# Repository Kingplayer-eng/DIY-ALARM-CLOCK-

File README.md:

# DIY-ALARM-CLOCK-
A Hardware project!!
So basically its a esp32 powered alarm clock that will show time and ring alarm in morning or anytime . There is 3.5 inch tft screen with can be use by either touch or by joystick. It has a motion detector at top - Adafruit sensor it sense hand and shut of alarm . There is also a kill switch at back which can turn off everything . It will be powered by lipo rechargeable batteries and charging module to charge it of course. I will not add buzzer as it literally irritate your hearing instead i added a amplifier with speaker . 
- I made this project specifically to lock in . I cannot wake up early with phone and then start scrolling which is really bad so i better try this .

- 
-
-
-

-PCB

-Schematic diagram

-Extra Information

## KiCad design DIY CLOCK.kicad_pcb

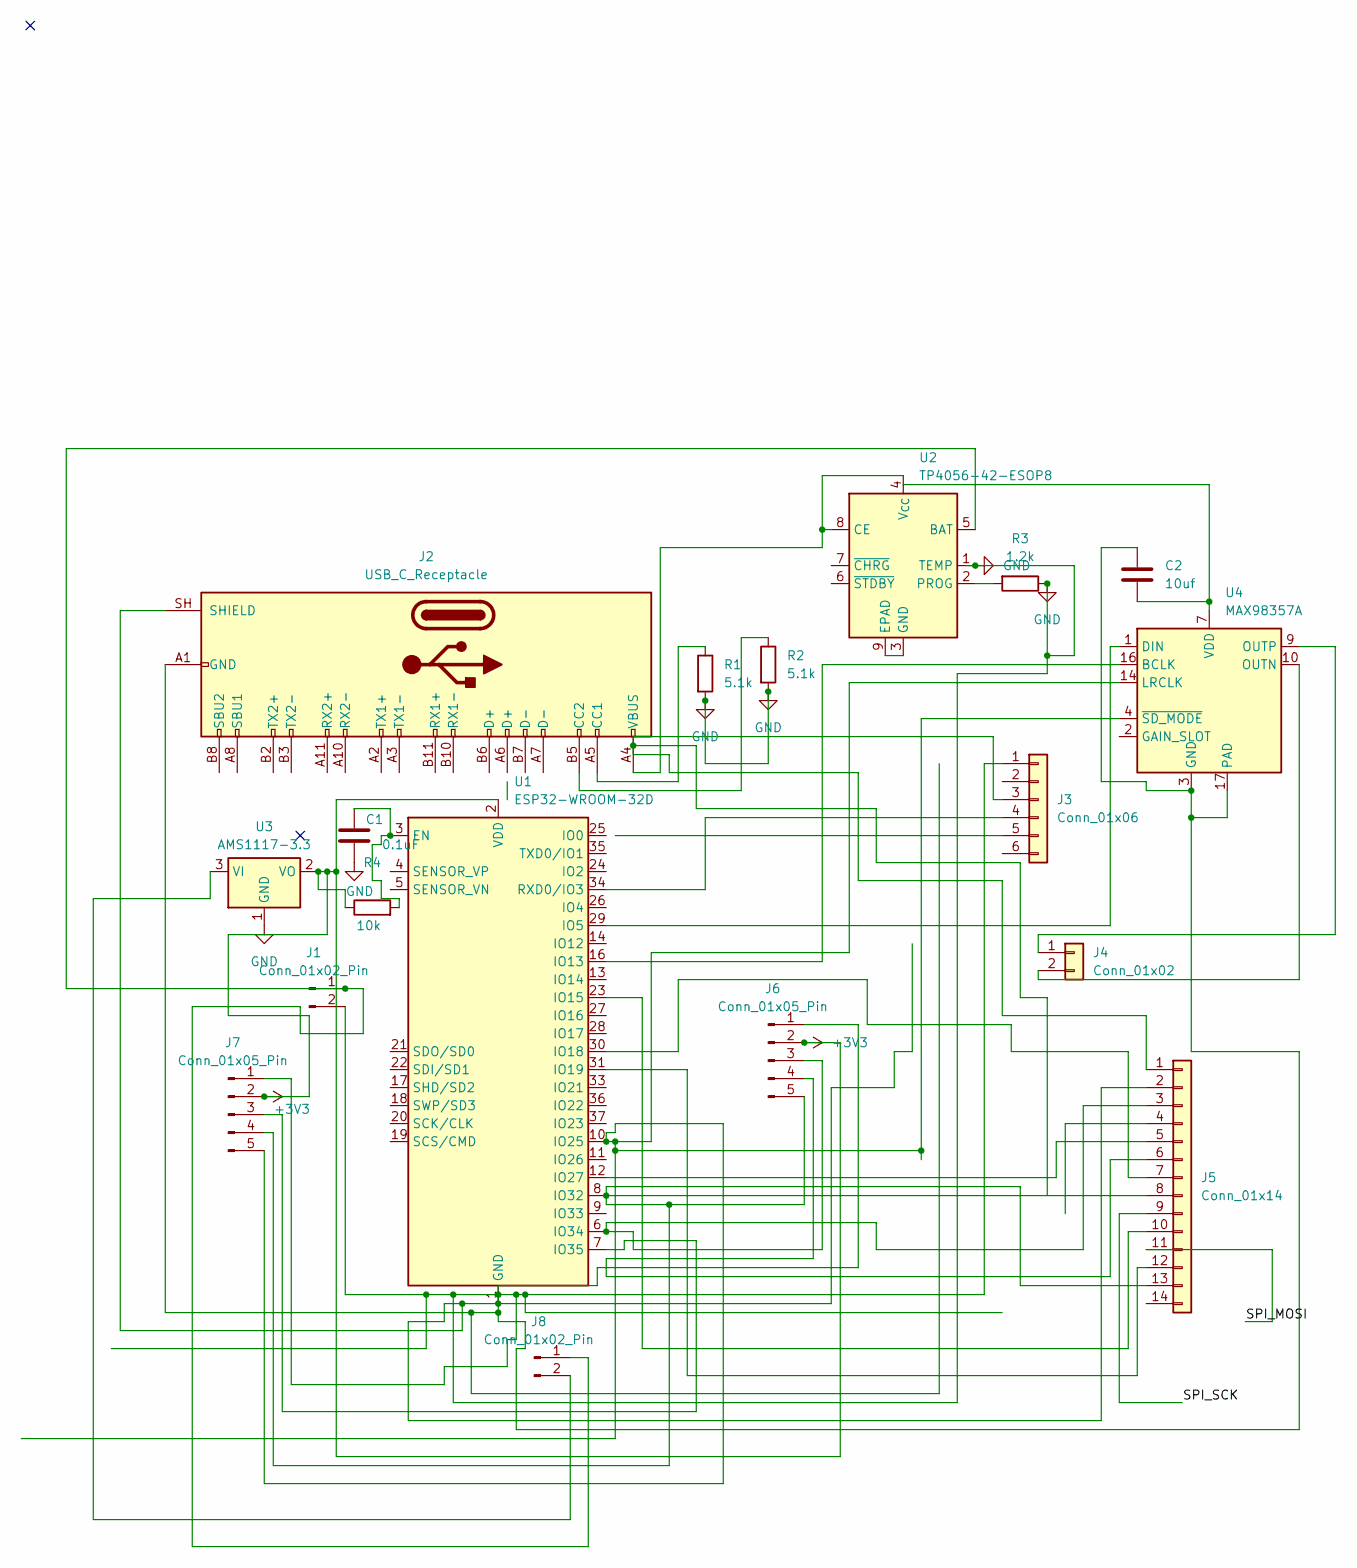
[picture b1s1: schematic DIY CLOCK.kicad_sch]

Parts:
C1: 0.1uF; C_0805_2012Metric
C2: 10uf; C_0805_2012Metric
J1: Conn_01x02_Pin; PinHeader_1x02_P2.54mm_Vertical_SMD_Pin1Left
J2: USB_C_Receptacle; USB_C_Receptacle_HRO_TYPE-C-31-M-12
J3: Conn_01x06
J4: Conn_01x02
J5: Conn_01x14; PinHeader_1x14_P2.54mm_Vertical
J6, J7: Conn_01x05_Pin; PinHeader_1x05_P2.54mm_Vertical
J8: Conn_01x02_Pin; PinHeader_1x02_P2.54mm_Vertical
R1, R2: 5.1k; R_0805_2012Metric_Pad1.20x1.40mm_HandSolder
R3: 1.2k; R_0805_2012Metric_Pad1.20x1.40mm_HandSolder
R4: 10k; R_0805_2012Metric
U1: ESP32-WROOM-32D
U2: TP4056-42-ESOP8; SOIC-8-1EP_3.9x4.9mm_P1.27mm_EP2.41x3.3mm_ThermalVias
U3: AMS1117-3.3; SOT-223-3_TabPin2
U4: MAX98357A; TQFN-16-1EP_3x3mm_P0.5mm_EP1.23x1.23mm

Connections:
+3V3: J6.2, J7.2, R4.1, U1.2 (VDD), U3.2 (VO)
/SPI_MOSI: J5.11
/SPI_SCK: J5.9
GND: C1.2, C2.1, J1.2, J2.A1 (GND), J2.A12 (GND), J2.B1 (GND), J2.B12 (GND), J2.SH (SHIELD), J3.1, J5.2, J6.1, J7.1, R1.2, R2.2, R3.1, U1.1 (GND), U1.15 (GND), U1.38 (GND), U1.39 (GND), U2.1 (TEMP), U3.1 (GND), U4.3 (GND), U4.11 (GND), U4.15 (GND), U4.17 (PAD)
unnamed: C2.2, U4.7 (VDD), U4.8 (VDD)
unnamed: J1.1, J8.1, U2.5 (BAT)
unnamed: J2.A5 (CC1), R1.1
unnamed: J2.B5 (CC2), R2.1
unnamed: J3.3, J5.1
unnamed: J3.4, U1.34 (RXD0/IO3)
unnamed: J4.1, U4.9 (OUTP)
unnamed: J4.2, U4.10 (OUTN)
unnamed: J5.3, J6.3, U1.6 (IO34)
unnamed: J5.5, U1.12 (IO27)
unnamed: J5.6, J6.4
unnamed: J5.7, U1.30 (IO18)
unnamed: J5.10, U1.23 (IO15)
unnamed: J5.12, U1.31 (IO19)
unnamed: J5.8, J5.13, J6.5, J7.4, U1.8 (IO32)
unnamed: J7.3, U1.7 (IO35)
unnamed: J7.5, U1.10 (IO25), U4.4 (~SD_MODE), U4.14 (LRCLK)
unnamed: J8.2, U3.3 (VI)
unnamed: C1.1, R4.2, U1.3 (EN)
unnamed: U1.29 (IO5), U4.1 (DIN)
unnamed: U1.16 (IO13), U4.16 (BCLK)
unnamed: J2.A4 (VBUS), J2.A9 (VBUS), J2.B4 (VBUS), J2.B9 (VBUS), U2.4 (V_{CC}), U2.8 (CE)
unnamed: U2.3 (GND), U2.9 (EPAD)
unnamed: R3.2, U2.2 (PROG)

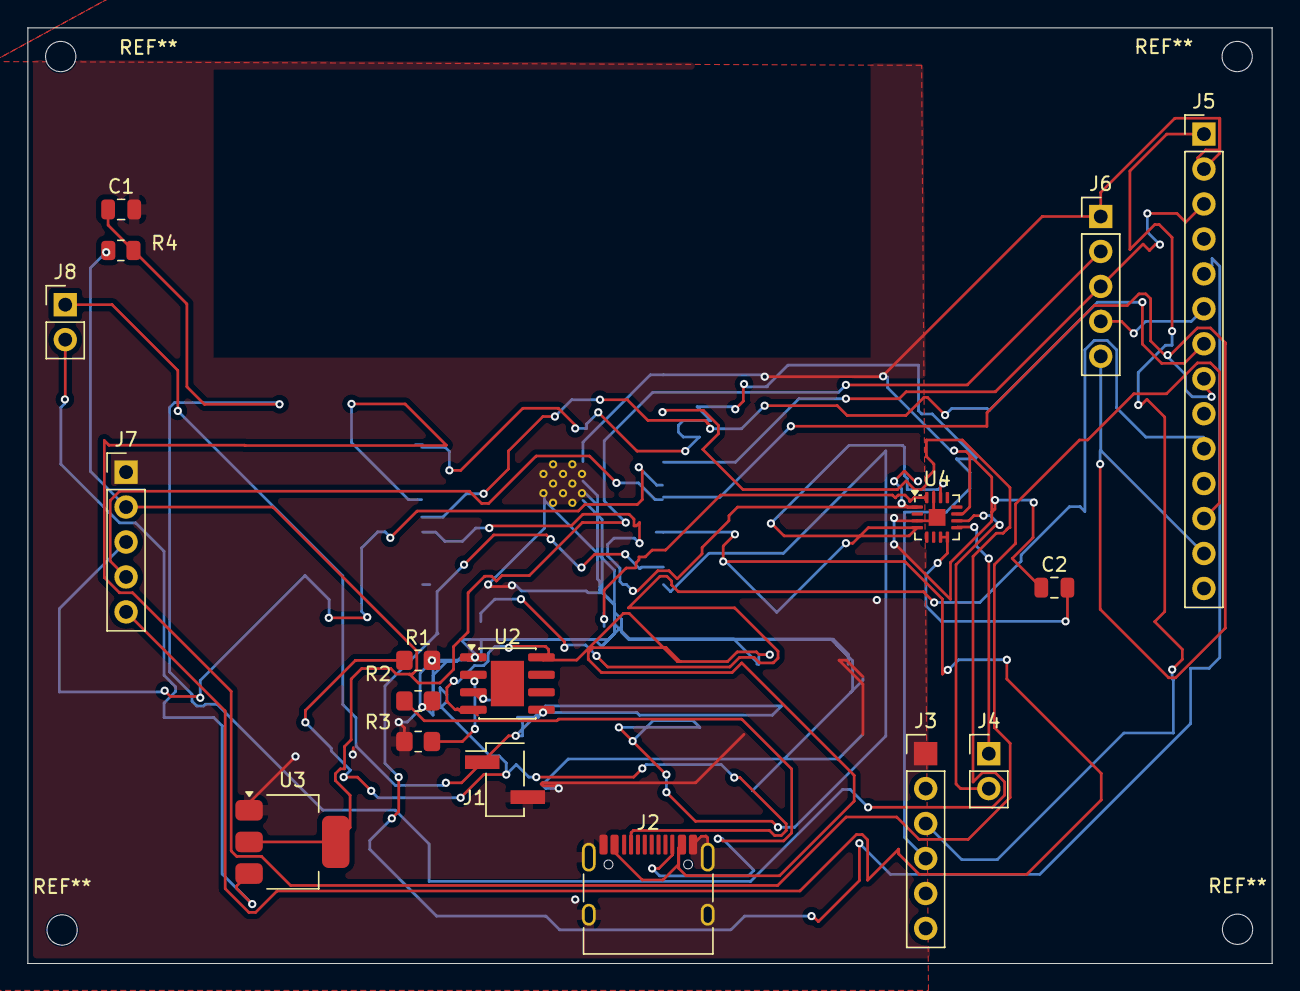
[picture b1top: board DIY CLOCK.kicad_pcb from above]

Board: 2 copper layers, 90.4 x 68.0 mm, 18 parts (1 on the bottom side), 26 nets.
